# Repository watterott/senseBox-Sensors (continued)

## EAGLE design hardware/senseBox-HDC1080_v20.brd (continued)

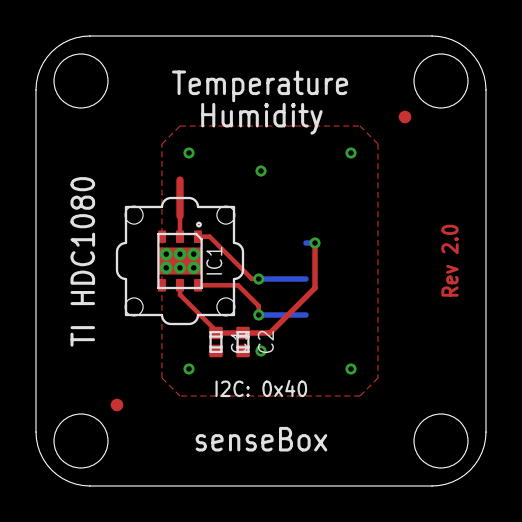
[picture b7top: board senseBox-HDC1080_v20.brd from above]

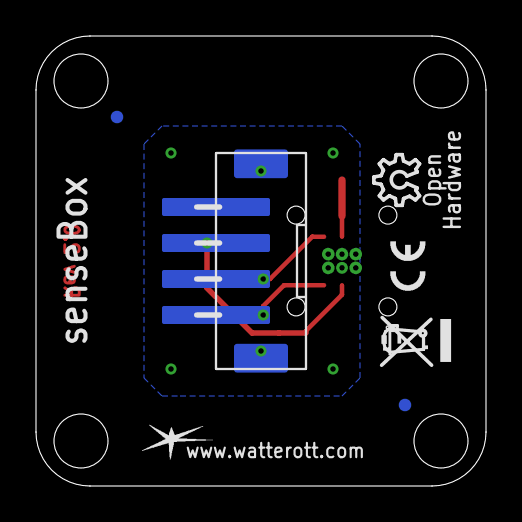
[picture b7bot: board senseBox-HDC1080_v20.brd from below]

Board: 2 copper layers, 25.0 x 25.0 mm, 9 parts (2 on the bottom side), 4 nets.

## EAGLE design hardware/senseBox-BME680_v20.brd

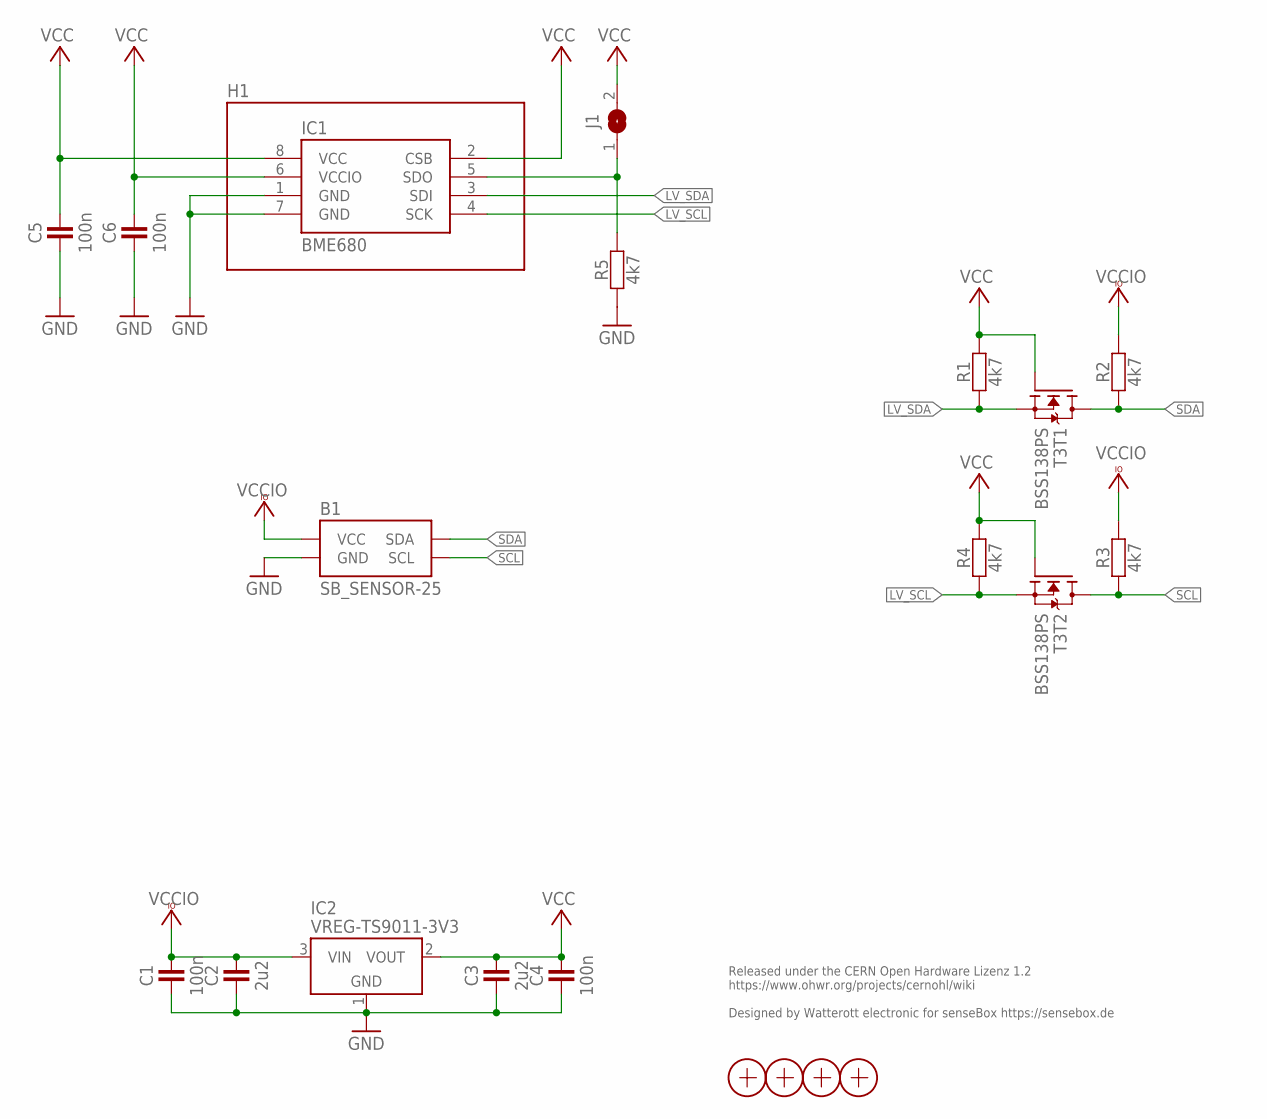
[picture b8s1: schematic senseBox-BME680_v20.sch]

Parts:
B1: SB_SENSOR-25; SB-25X25
C1, C4, C5, C6: 100n; C0402
C2, C3: 2u2; C0402
H1: SF2
IC1: BME680
IC2: VREG-TS9011-3V3; SOT23
J1: JUMPER2-0402-NC; JUMPER2-0402_NC
R1, R2, R3, R4, R5: 4k7; C0402
T3: BSS138PS; SOT363
X1, X2, X3, X4: PASSER-07; PASSER_07MM

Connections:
GND: B1.GND, C1.1, C2.1, C3.1, C4.1, C5.1, C6.1, IC1.1 (GND), IC1.7 (GND), IC2.1 (GND), R5.1
LV_SCL: IC1.4 (SCK), R4.1, T3.4 (S)
LV_SDA: IC1.3 (SDI), R1.1, T3.1 (S)
LV_SDO: IC1.5 (SDO), J1.1, R5.2
SCL: B1.SCL, R3.1, T3.3 (D)
SDA: B1.SDA, R2.1, T3.6 (D)
VCC: C3.2, C4.2, C5.2, C6.2, IC1.2 (CSB), IC1.6 (VCCIO), IC1.8 (VCC), IC2.2 (VOUT), J1.2, R1.2, R4.2, T3.2 (G), T3.5 (G)
VCCIO: B1.VCC, C1.2, C2.2, IC2.3 (VIN), R2.2, R3.2

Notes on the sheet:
Released under the CERN Open Hardware Lizenz 1.2 https://www.ohwr.org/projects/cernohl/wiki Designed by Watterott electronic for senseBox https://sensebox.de

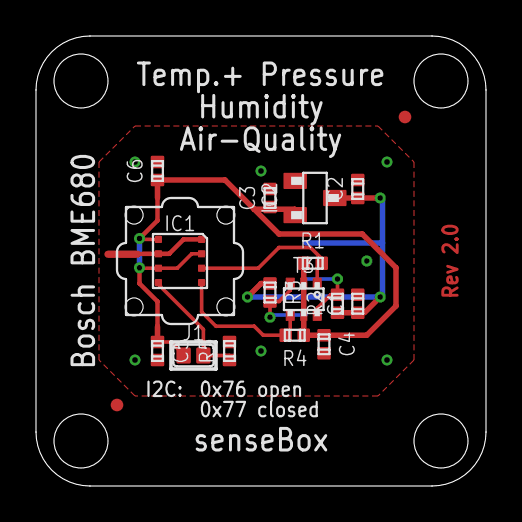
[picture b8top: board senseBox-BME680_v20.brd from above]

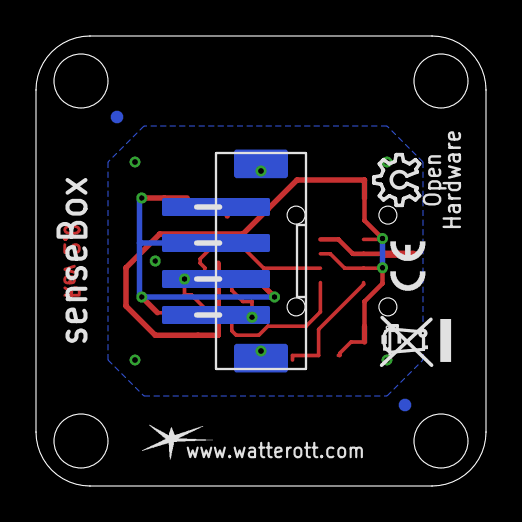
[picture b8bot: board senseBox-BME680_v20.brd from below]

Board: 2 copper layers, 25.0 x 25.0 mm, 21 parts (2 on the bottom side), 8 nets.

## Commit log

2018-03-02 added readme
2018-05-03 added layout and schematics
2018-07-07 updated schematics
2020-05-28 added v2.1
2020-10-29 added senseBox-SCD30 CO2 sensor
2022-07-13 add RTC-RV8523
2022-07-13 update senseBox_I2C-Multiplexer_V11
2023-06-06 added V22
